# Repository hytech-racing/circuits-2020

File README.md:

# 2020 Circuits

Repository for all of the circuits for the 2019-2020 car.

## Getting Started with this Git Repository
1. Follow HyTech's [Software Guide](https://github.com/hytech-racing/training/tree/master/Resources).
2. Create a GitHub account if you don't already have one.
3. Download and install [GitHub Desktop](https://desktop.github.com/) (basic) or [Git CLI](https://git-scm.com/book/en/v2/Getting-Started-Installing-Git) (advanced).
    * If you are using GitHub Desktop for the first time, be sure to read the [User Guide](https://help.github.com/desktop/guides/).
    * If you are using Git for the first time, you should start off by reading a tutorial. There are many available online:
        * [Pro Git book](https://git-scm.com/book/en/v2)
        * [Atlassian Git Tutorial](https://www.atlassian.com/git/tutorials/)
    * You may want to keep a copy of [GitHub's Git Cheat Sheet](https://services.github.com/kit/downloads/github-git-cheat-sheet.pdf) as a reference.
4. Talk to your subteam lead to be added to the team within the GitHub organization.
5. Clone this repository to your computer using the URLs:
    * SSH: `git@github.com:hytech-racing/circuits-2020.git`
    * HTTPS: `https://github.com/hytech-racing/circuits-2020.git`

## Getting Started with EAGLE
1. Follow HyTech's [Software Guide](https://github.com/hytech-racing/training/tree/master/Resources).
2. Download and install [EAGLE](https://www.autodesk.com/products/eagle/overview)
3. Get the free [Educational License](https://www.autodesk.com/education/free-software/eagle) (a .edu email address is required)

## Circuit Board Versioning Scheme
* New boards must start their numbering at revision 1.
* Revision numbers must be incremented by 1 when a physical board is manufactured, but not at any other time.
* After a board is manufactured, the files corresponding to the manufactured version should not be modified.
* Circuit boards based off of a previous year's design should increment based off of the previous board's revision number.

## More Information
* [Software Guide](https://github.com/hytech-racing/training/tree/master/Resources)
* [Team Site](https://hytechracing.gatech.edu/)
* [Facebook](https://www.facebook.com/HyTechRacing/)
* [Engage](https://gatech.campuslabs.com/engage/organization/hytech-racing)

## License
This project is licensed under the GPL License v3.0. See the [LICENSE](LICENSE) file for more information.

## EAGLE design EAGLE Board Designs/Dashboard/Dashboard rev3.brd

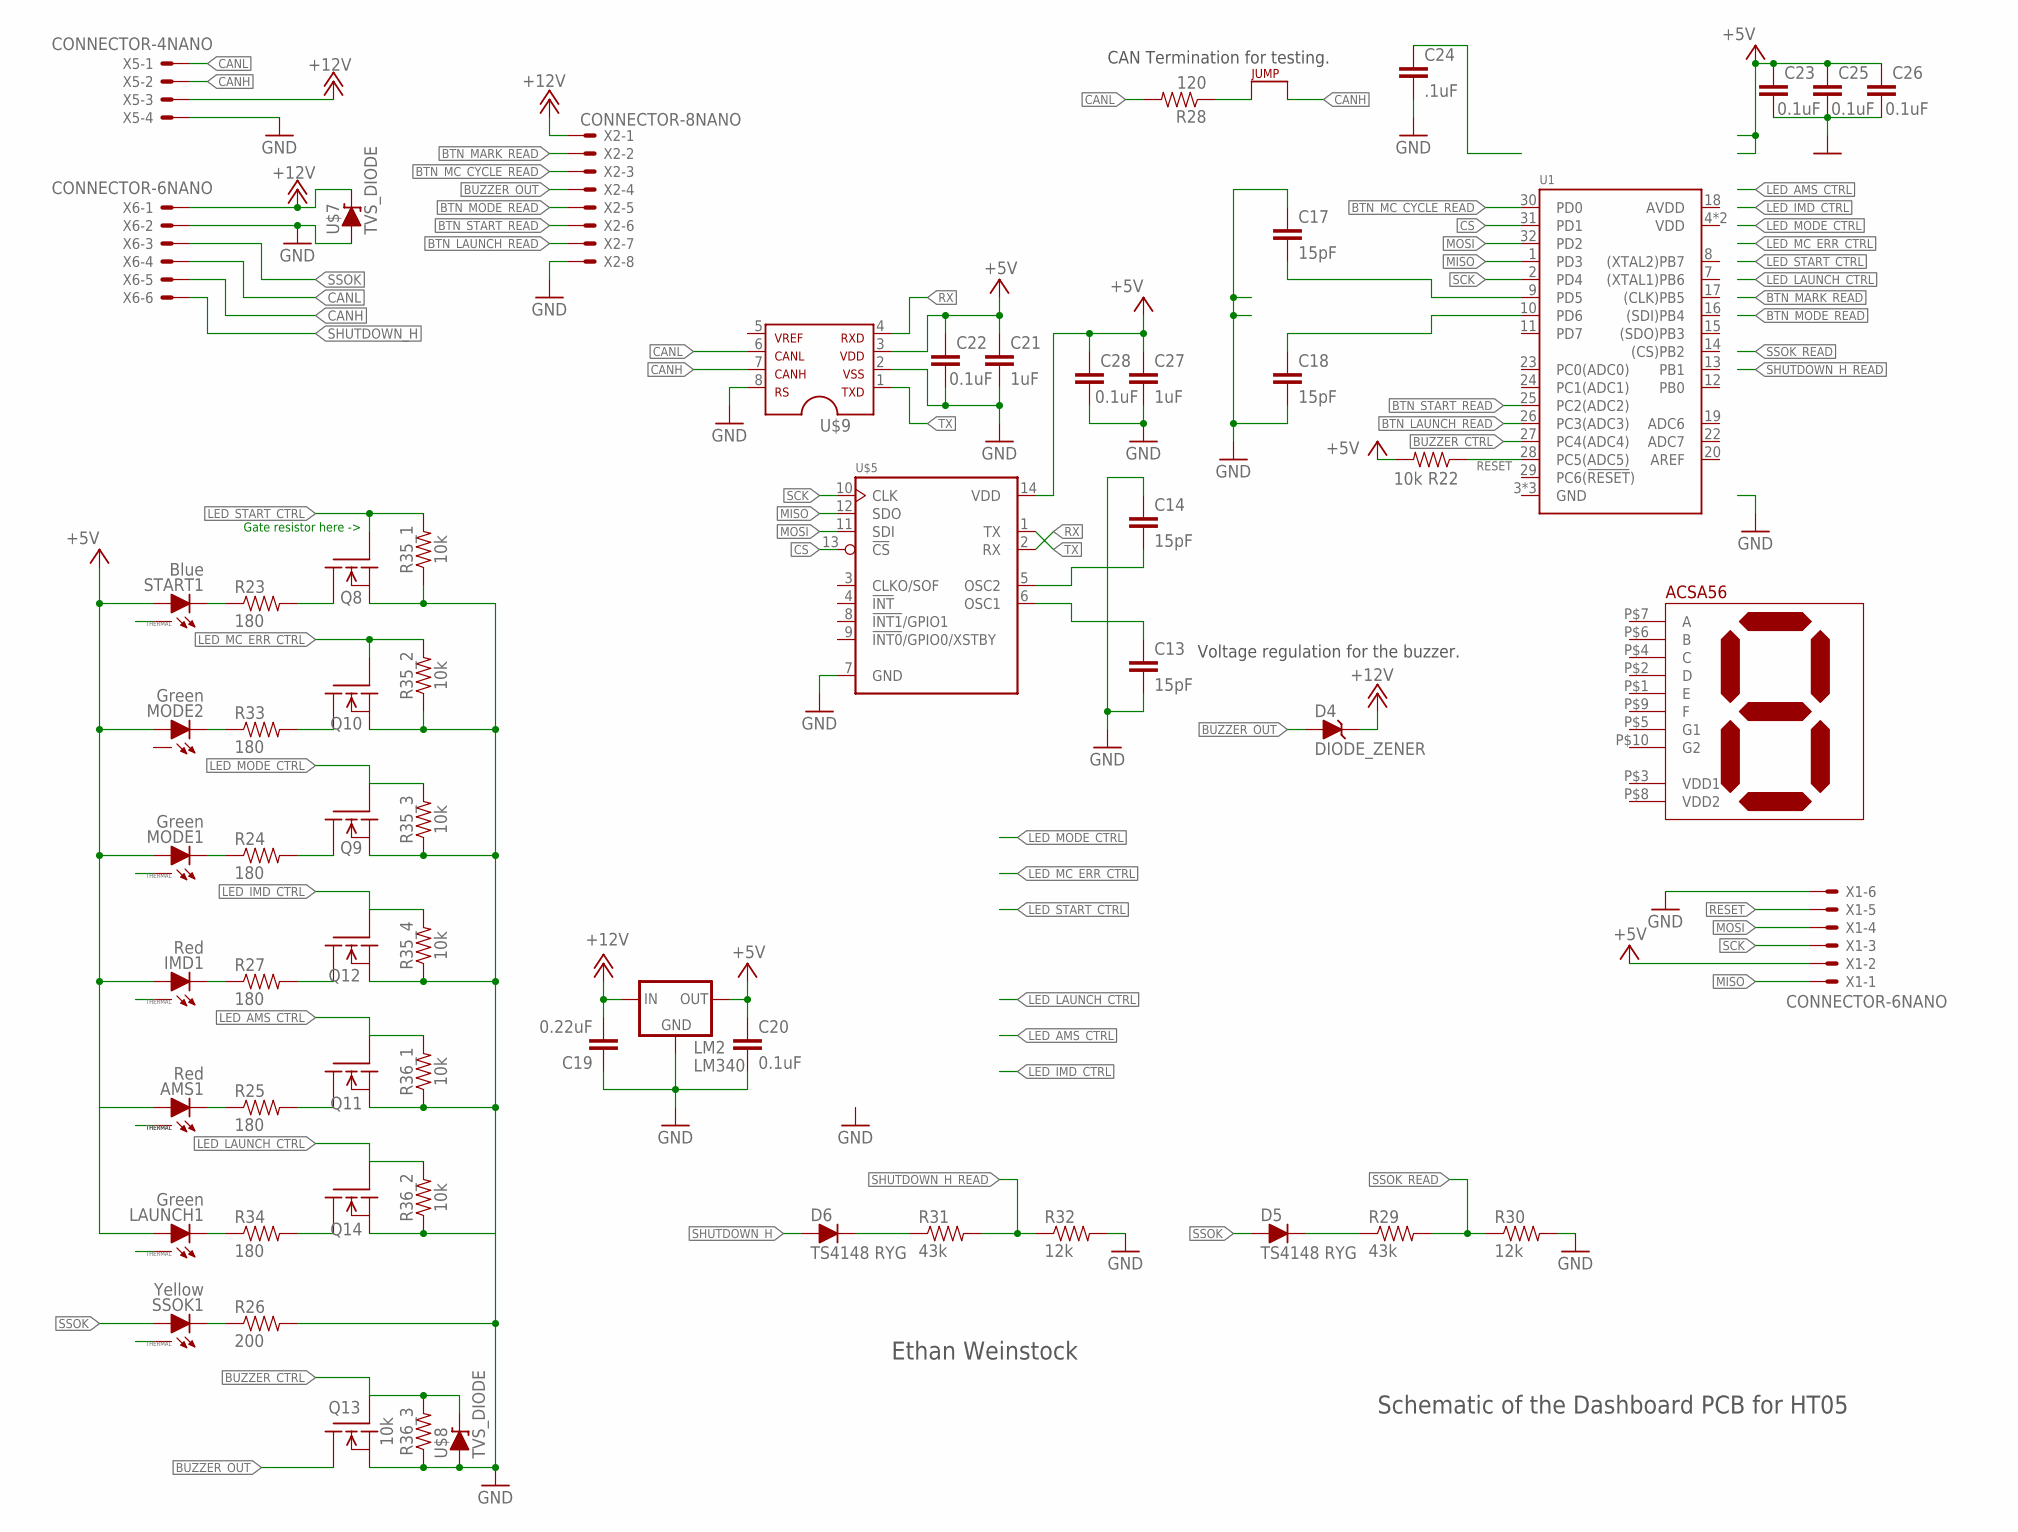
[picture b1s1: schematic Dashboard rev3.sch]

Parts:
AMS1: Red; XP-E2
C13, C14, C17, C18: 15pF; 0603-CAP
C19: 0.22uF; 0603-CAP
C20, C22, C23, C25, C26, C28: 0.1uF; 0603-CAP
C21, C27: 1uF; 0603-CAP
C24: .1uF; 0603-CAP
D4: DIODE_ZENER; SOT23
D5, D6: TS4148 RYG; 0805_D
IMD1: Red; XP-E2
J4: JUMPER0603; 0603-JUMP
LAUNCH1: Green; XP-E2
LM2: LM340; SOT223
MODE1, MODE2: Green; XP-E2
Q8, Q9, Q10, Q11, Q12, Q13, Q14: DMG3406LSOT; SOT23
R22: 10k; 0603-RES
R23, R24, R25, R27, R33, R34: 180; 0603-RES
R26: 200; 0805
R28: 120; 0603-RES
R29, R31: 43k; 0603-RES
R30, R32: 12k; 0603-RES
R35, R36: 10k; CAT16-*4
SSOK1: Yellow; XP-E2
START1: Blue; XP-E2
U1: ATMEGA328P-AU; TQFP-32
U$1: ACSA56-51CGKWA
U$5: MCP2518FD; SOIC-14
U$7, U$8: TVS_DIODE; U-DFN1608-2
U$9: MCP2562FD; SOIC-08
X1, X6: CONNECTOR-6NANO; MOLEX_NANOFIT_SMD_06
X2: CONNECTOR-8NANO; MOLEX_NANOFIT_SMD_08
X5: CONNECTOR-4NANO; MOLEX_NANOFIT_SMD_04

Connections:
+5V: C20.1, C21.1, C22.1, C23.1, C25.1, C26.1, C27.1, C28.1, LM2.3 (OUT), R22.2, U$5.14 (VDD), U$9.3, X1.2
+5V1: AMS1.A, IMD1.A, LAUNCH1.A, MODE1.A, MODE2.A, START1.A
+12V: C19.2, D4.3 (C), LM2.1 (IN), U$7.P$2 (C), X2.1, X5.3, X6.1
AVDD: U1.18 (AVDD)
BTN_LAUNCH_READ: U1.26 (PC3(ADC3)), X2.7
BTN_MARK_READ: X2.2
BTN_MC_CYCLE_READ: U1.30 (PD0), X2.3
BTN_MODE_READ: X2.5
BTN_START_READ: U1.25 (PC2(ADC2)), X2.6
BUZZER_CTRL: Q13.1 (G), R36.P$6 (2), U1.27 (PC4(ADC4)), U$8.P$2 (C)
BUZZER_OUT: D4.1 (A), Q13.3 (D), X2.4
CANH: J4.2, U$9.7, X5.2, X6.5
CANL: R28.2, U$9.6, X5.1, X6.4
CS: U1.31 (PD1), U$5.13 (!CS)
GND: C13.2, C14.1, C17.1, C18.2, C19.1, C20.2, C23.2, C24.2, C25.2, C26.2, C27.2, C28.2, LM2.2 (GND), LM2.4 (GND), Q8.2 (S), Q9.2 (S), Q10.2 (S), Q11.2 (S), Q12.2 (S), Q13.2 (S), R26.2, R30.2, R32.2, R35.P$1 (1), R35.P$2 (1), R35.P$3 (1), R35.P$4 (1), R36.P$1 (1), R36.P$3 (1), U1.3 (GND), U1.5 (GND), U1.21 (GND), U$5.7 (GND), U$7.P$1 (A), U$8.P$1 (A), U$9.8, X1.6, X2.8, X5.4, X6.2
GND2: Q14.2 (S), R36.P$2 (1)
LED_AMS_CTRL: Q11.1 (G), R36.P$8 (2)
LED_IMD_CTRL: Q12.1 (G), R35.P$5 (2)
LED_LAUNCH_CTRL: Q14.1 (G), R36.P$7 (2)
LED_MC_ERR_CTRL: Q10.1 (G), R35.P$7 (2)
LED_MODE_CTRL: Q9.1 (G), R35.P$6 (2)
LED_START_CTRL: Q8.1 (G), R35.P$8 (2)
MISO: U1.1 (PD3), U$5.12 (SDO), X1.1
MOSI: U1.32 (PD2), U$5.11 (SDI), X1.4
unnamed: C13.1, U$5.6 (OSC1)
unnamed: MODE2.C, R33.1
unnamed: C17.2, U1.9 (PD5)
unnamed: C18.1, U1.10 (PD6)
unnamed: MODE1.C, R24.1
unnamed: IMD1.C, R27.1
unnamed: R26.1, SSOK1.C
unnamed: AMS1.C, R25.1
unnamed: R23.1, START1.C
unnamed: D5.C, R29.1
unnamed: D6.C, R31.1
unnamed: Q8.3 (D), R23.2
unnamed: Q10.3 (D), R33.2
unnamed: Q9.3 (D), R24.2
unnamed: Q12.3 (D), R27.2
unnamed: Q11.3 (D), R25.2
unnamed: J4.1, R28.1
unnamed: LAUNCH1.C, R34.1
unnamed: Q14.3 (D), R34.2
unnamed: C14.2, C21.2, C22.2, U$5.5 (OSC2), U$9.2
RESET: R22.1, U1.28 (PC5(ADC5)), X1.5
RX: U$5.2 (RX), U$9.4
SCK: U1.2 (PD4), U$5.10 (CLK), X1.3
SHUTDOWN_H: D6.A, X6.6
SHUTDOWN_H_READ: R31.2, R32.1
SSOK: D5.A, SSOK1.A, X6.3
SSOK_READ: R29.2, R30.1
THERMAL: AMS1.X, IMD1.X, LAUNCH1.X, MODE1.X, SSOK1.X, START1.X
TX: U$5.1 (TX), U$9.1
VDD: U1.4 (VDD), U1.6 (VDD)

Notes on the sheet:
Ethan Weinstock
Schematic of the Dashboard PCB for HT05
Voltage regulation for the buzzer.
CAN Termination for testing.
Gate resistor here ->

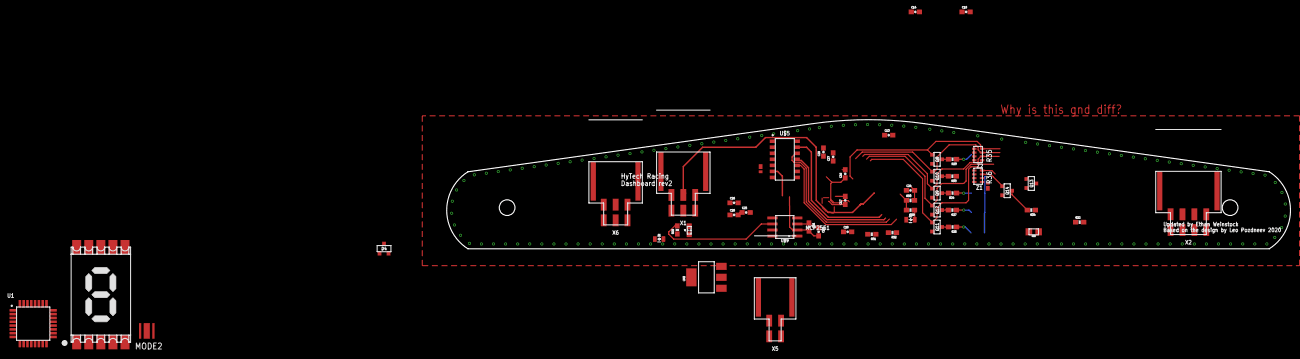
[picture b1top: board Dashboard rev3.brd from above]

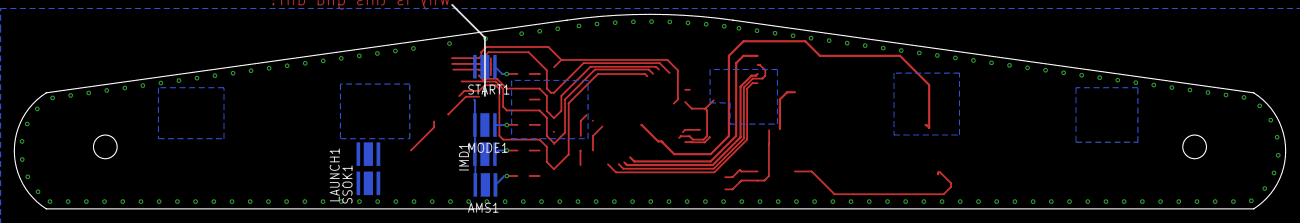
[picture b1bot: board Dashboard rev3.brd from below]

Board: 2 copper layers, 177.4 x 27.1 mm, 58 parts (6 on the bottom side), 51 nets.

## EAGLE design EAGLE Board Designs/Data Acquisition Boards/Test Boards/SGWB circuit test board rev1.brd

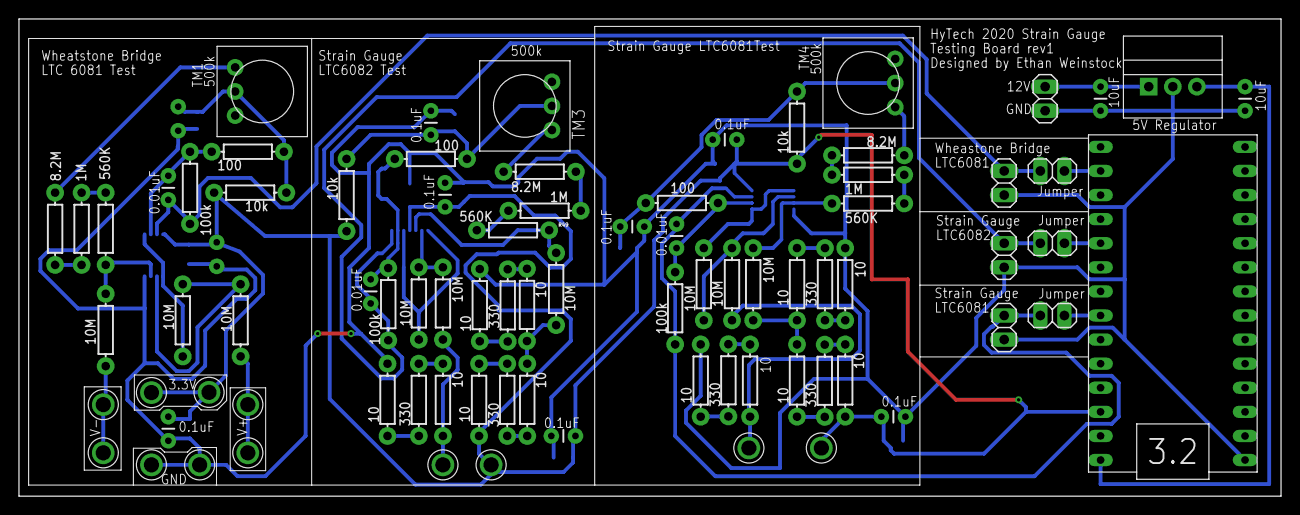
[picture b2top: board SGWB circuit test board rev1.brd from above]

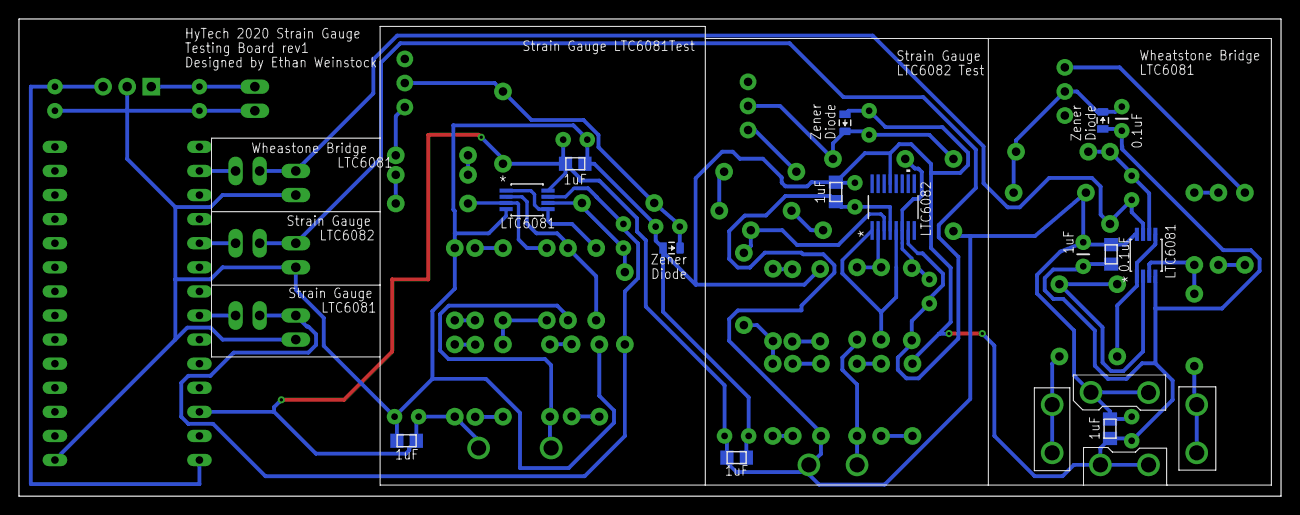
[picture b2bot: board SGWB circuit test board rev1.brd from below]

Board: 2 copper layers, 133.1 x 50.3 mm, 95 parts (14 on the bottom side), 52 nets.

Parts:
C1: 0.1uF; 0805
C2, C14, C29: 0.01uF; CAP-PTH-SMALL
C3, C11, C15, C17, C21, C26, C28, C30: 0.1uF; CAP-PTH-SMALL
C4: 1uF; CAP-PTH-SMALL
C5, C6: 10uF; CAP-PTH-SMALL
C12, C16, C22, C27, C31: 1uF; 0805
J1, J2, J3: JUMPER.1; 1X02
JP1, JP2, JP3, JP4: M02; 1X02
LT1790B, LT1790B2: 1.25V; 0805_D
LT1790B3: DIODE_ZENER0805; 0805_D
R1, R2, R4, R18, R19, R21, R29, R33, R35: 10M; AXIAL-0.3
R3, R20, R34: 8.2M; AXIAL-0.3
R5, R22, R36: 100k; AXIAL-0.3
R6, R23, R37: 100; AXIAL-0.3
R7, R24, R38: 10k; AXIAL-0.3
R8, R15, R16, R17, R25, R28, R31, R32, R40, R42, R43, R45: 10; AXIAL-0.3
R26, R27, R39, R41, R44, R46: 330; AXIAL-0.3
R47, R49, R53: 1M; AXIAL-0.3
R48, R50, R54: 560K; AXIAL-0.3
REG: 5V; OKI-78SR
TM1, TM3, TM4: 500k; TRIM-3386
U1: LTC6082CGNPBF; SSOP-16_GN
U$1, U$9: LTC6081; MSOP-8_MS
U$2: TEENSY_3.2_SIMPLE
U$5, U$6, U$8, U$10, U$11, U$12, U$13, U$14, U$15, U$16, U$17, U$18: TEST_POINT

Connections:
3V3: C1.2, C4.1, C11.1, C12.1, C15.2, C16.1, C21.1, C22.1, C26.1, C27.1, C28.2, C31.1, R7.P$2, R24.P$2, R25.P$1, R28.P$1, R38.P$2, U1.4, U$1.8, U$2.3.3V, U$5.P$1, U$8.P$1, U$9.8, U$11.P$1, U$18.P$1
+5V: C6.2, REG.3, U$2.VIN
+12V: C5.2, JP2.2, REG.1
GND: C1.1, C3.1, C4.2, C5.1, C6.1, C11.2, C12.2, C15.1, C16.2, C17.1, C21.2, C22.2, C26.2, C27.2, C28.1, C30.1, C31.2, JP1.1, JP2.1, JP3.1, JP4.1, LT1790B.A, LT1790B2.A, LT1790B3.A, R40.P$2, R42.P$1, R43.P$2, R45.P$1, REG.2, U1.13, U$1.4, U$2.GND, U$9.4, U$14.P$1, U$15.P$1
INB-: C2.1, R5.P$1, R6.P$2, U$1.6
INB-3: C29.1, R36.P$1, R37.P$2, U$9.6
unnamed: R1.P$2, R4.P$2, U$1.2
unnamed: R2.P$2, R54.P$1, U$1.3
unnamed: C3.2, LT1790B.C, R6.P$1, R7.P$1, TM1.2
unnamed: J1.1, U$2.A0
unnamed: R3.P$2, TM1.1
unnamed: J2.1, U$2.A3
unnamed: J3.1, U$2.A6
unnamed: R16.P$2, R17.P$2, R19.P$1
unnamed: C17.2, LT1790B2.C, R23.P$1, R24.P$1, TM3.2
unnamed: R20.P$2, TM3.1
unnamed: R8.P$2, R26.P$1
unnamed: R27.P$2, R32.P$1
unnamed: R31.P$1, R41.P$2
unnamed: R16.P$1, R44.P$2
unnamed: R31.P$2, R32.P$2, R33.P$1
unnamed: R17.P$1, R39.P$2
unnamed: R25.P$2, R41.P$1
unnamed: R29.P$2, R35.P$2, U$9.2
unnamed: R33.P$2, R48.P$1, U$9.3
unnamed: C30.2, LT1790B3.C, R37.P$1, R38.P$1, TM4.2
unnamed: R34.P$2, TM4.1
unnamed: R26.P$2, R43.P$1
unnamed: R27.P$1, R42.P$2
unnamed: R28.P$2, R44.P$1
unnamed: R39.P$1, R45.P$2
unnamed: R15.P$2, R46.P$1
unnamed: R40.P$1, R46.P$2
unnamed: R34.P$1, R47.P$1
unnamed: R47.P$2, R48.P$2
unnamed: R20.P$1, R49.P$1
unnamed: R49.P$2, R50.P$2
unnamed: R3.P$1, R53.P$1
unnamed: R53.P$2, R54.P$2
OUT1: R4.P$1, U$1.1, U$1.5
OUT3: R35.P$1, U$9.1, U$9.5
OUT4: R21.P$1, U1.1, U1.5
OUT4A+: R19.P$2, R50.P$1, U1.3
OUT4A-: R18.P$2, R21.P$2, U1.2
V+1: R1.P$1, U$12.P$1, U$13.P$1
V-1: R2.P$1, U$16.P$1, U$17.P$1
VOUT1: C2.2, J1.2, JP1.2, R5.P$2, U$1.7
VOUT3: C29.2, J3.2, JP4.2, R36.P$2, U$9.7
VOUT4: C14.2, J2.2, JP3.2, R22.P$2, U1.7
VOUT4-: C14.1, R22.P$1, R23.P$2, U1.6
VR3-2: R8.P$1, R29.P$1, U$6.P$1
VR4-2: R15.P$1, R18.P$1, U$10.P$1

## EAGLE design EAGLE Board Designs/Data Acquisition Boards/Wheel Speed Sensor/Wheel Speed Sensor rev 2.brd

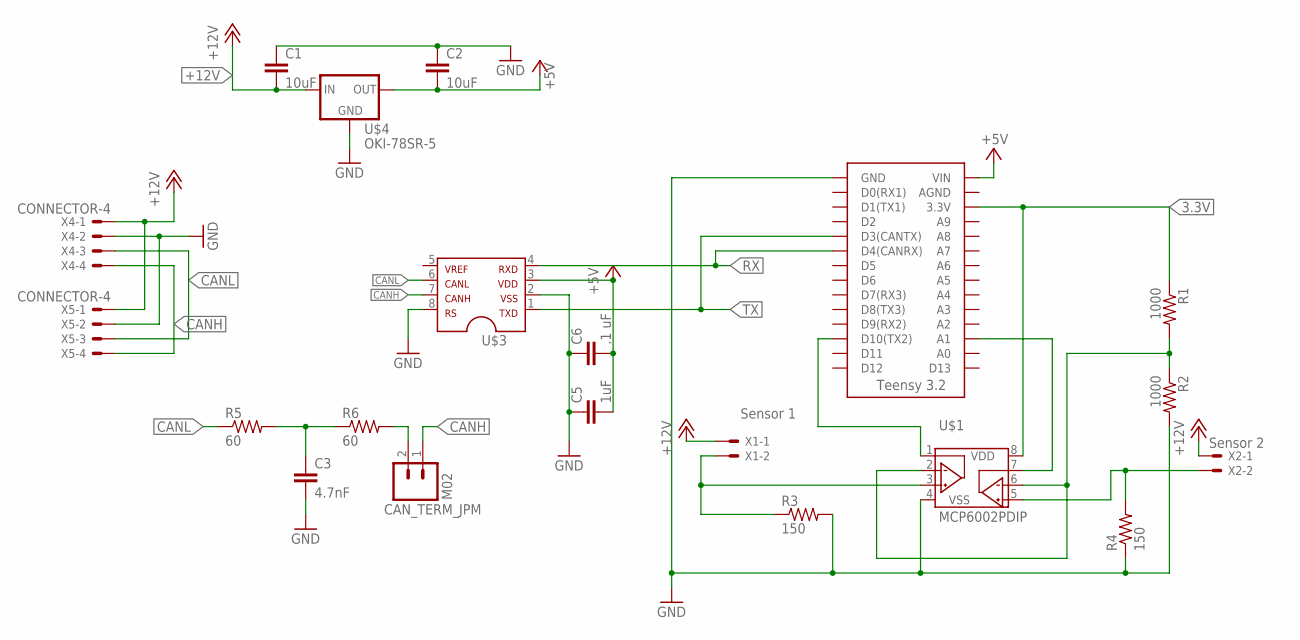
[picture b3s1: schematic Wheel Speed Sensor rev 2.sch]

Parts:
C1, C2: 10uF; CAP-PTH-5MM
C3: 4.7nF; CAP-PTH-5MM
C5: 1uF; CAP-PTH-5MM
C6: .1 uF; CAP-PTH-5MM
CAN_TERM_JPM: M02; 1X02
R1, R2: 1000; AXIAL-0.3
R3, R4: 150; AXIAL-0.3
R5, R6: 60; AXIAL-0.3
U$1: MCP6002PDIP; DIL08
U$2: TEENSY_3.2_SIMPLE
U$3: MCP2551; SOIC-08
U$4: OKI-78SR-5; OKI-78SR
X1: Sensor 1; MINIFIT_5566-2
X2: Sensor 2; MINIFIT_5566-2
X4, X5: CONNECTOR-4; MINIFIT_5566-4

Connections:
3.3V: R1.P$1 (1), U$1.8 (VDD), U$2.3.3V
+5V: C2.2, C5.2, C6.2, U$2.VIN, U$3.3, U$4.3 (OUT)
+12V: C1.2, U$4.1 (IN), X1.1, X2.1, X4.1, X5.1
CANH: CAN_TERM_JPM.1, U$3.7, X4.4, X5.4
CANL: R5.P$1 (1), U$3.6, X4.3, X5.3
GND: C1.1, C2.1, C3.2, C5.1, C6.1, R2.P$2 (2), R3.P$2 (2), R4.P$1 (1), U$1.4 (VSS), U$2.GND, U$3.2, U$3.8, U$4.2 (GND), X4.2, X5.2
unnamed: R1.P$2 (2), R2.P$1 (1), U$1.2 (VINA-), U$1.6 (VINB-)
unnamed: C3.1, R5.P$2 (2), R6.P$1 (1)
unnamed: R3.P$1 (1), U$1.3 (VINA+), X1.2
unnamed: U$1.7 (VOUTB), U$2.A1
unnamed: U$1.1 (VOUTA), U$2.D10(TX2)
unnamed: R4.P$2 (2), U$1.5 (VINB+), X2.2
unnamed: CAN_TERM_JPM.2, R6.P$2 (2)
RX: U$2.D4(CANRX), U$3.4
TX: U$2.D3(CANTX), U$3.1

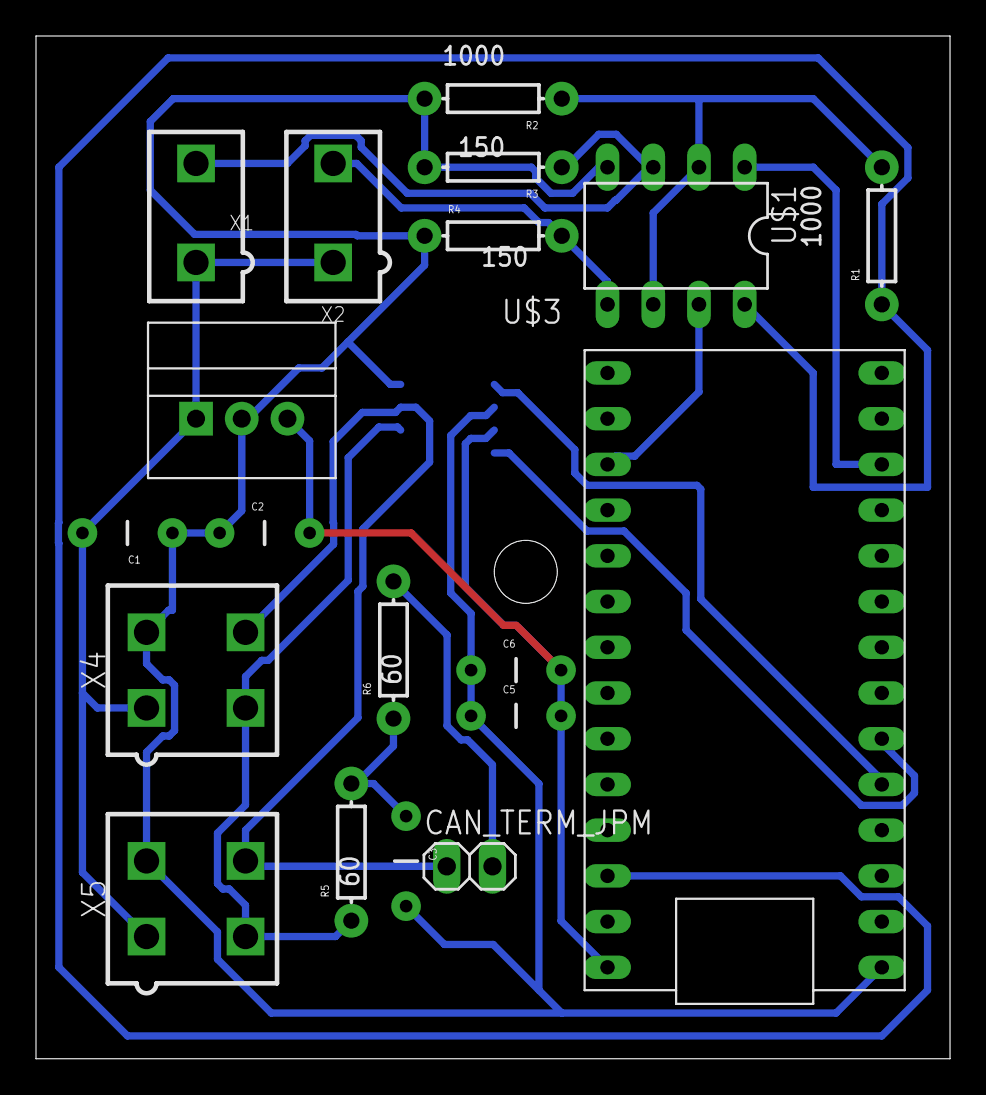
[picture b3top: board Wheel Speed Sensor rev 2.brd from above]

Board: 2 copper layers, 50.8 x 56.8 mm, 20 parts (1 on the bottom side), 15 nets.

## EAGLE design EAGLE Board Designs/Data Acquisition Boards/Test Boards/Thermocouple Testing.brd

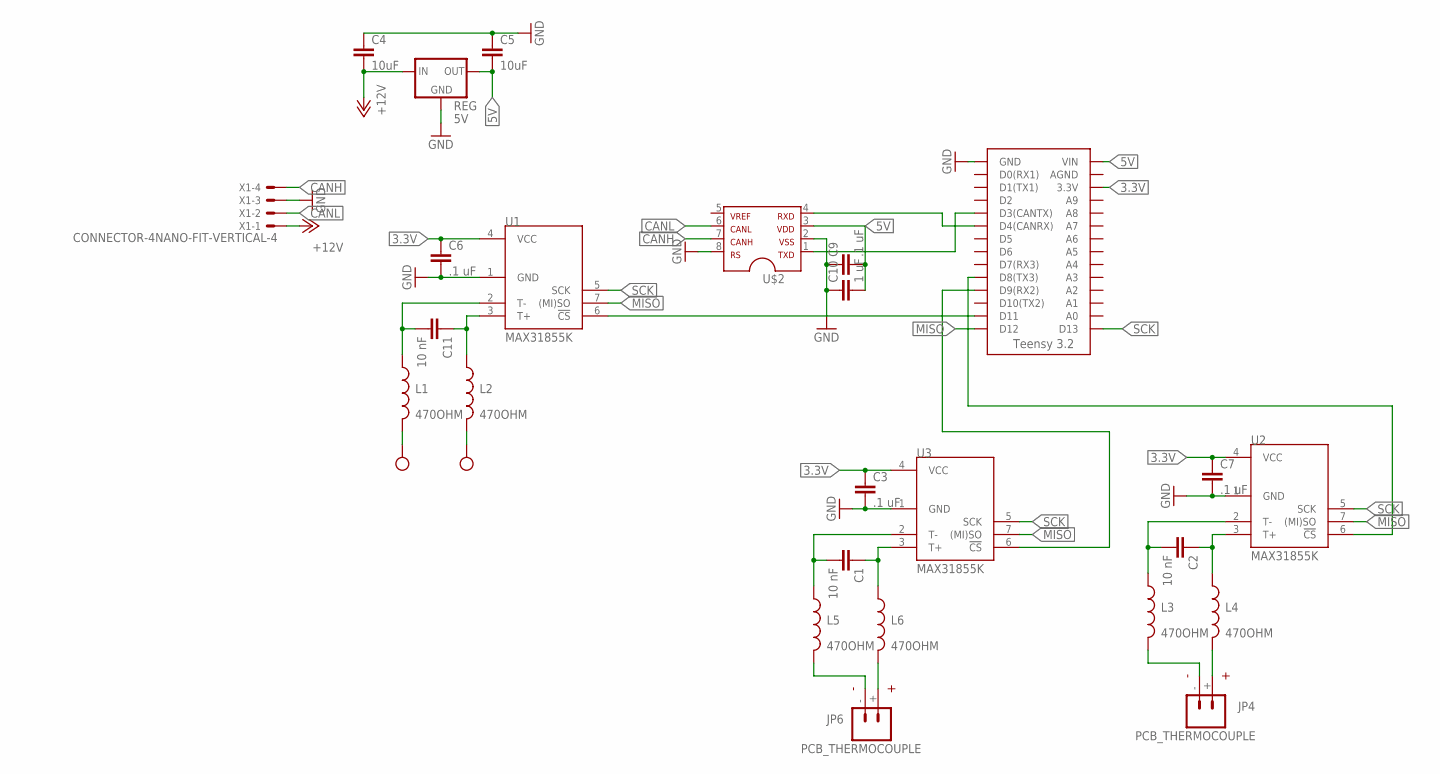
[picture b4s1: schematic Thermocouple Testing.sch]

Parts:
C1, C2, C11: 10 nF; AXIAL-5MM
C3, C6, C7, C9: .1 uF; AXIAL-5MM
C4, C5: 10uF; AXIAL-5MM
C10: 1 uF; AXIAL-5MM
JP4, JP6: PCB_THERMOCOUPLE; PCC-SMP
L1, L2, L3, L4, L5, L6: 470OHM; 0805
REG: 5V; OKI-78SR
U1, U2, U3: MAX31855K; SOIC8
U$1: TEENSY_3.2_SIMPLE
U$2: MCP2551DIL; DIL08
U$3, U$4: TEST_POINT
X1: CONNECTOR-4NANO-FIT-VERTICAL-4; NANO-FIT_VERTICAL-4

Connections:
3.3V: C3.P$1 (1), C6.P$1 (1), C7.P$1 (1), U1.4 (VCC), U2.4 (VCC), U3.4 (VCC), U$1.3.3V
5V: C5.P$2 (2), C9.P$2 (2), C10.P$2 (2), REG.3 (OUT), U$1.VIN, U$2.3
+12V: C4.P$2 (2), REG.1 (IN), X1.P$1
CANH: U$2.7, X1.P$4
CANL: U$2.6, X1.P$2
GND: C3.P$2 (2), C4.P$1 (1), C5.P$1 (1), C6.P$2 (2), C7.P$2 (2), C9.P$1 (1), C10.P$1 (1), REG.2 (GND), U1.1 (GND), U2.1 (GND), U3.1 (GND), U$1.GND, U$2.2, U$2.8, X1.P$3
MISO: U1.7 ((MI)SO), U2.7 ((MI)SO), U3.7 ((MI)SO), U$1.D12
unnamed: L1.2, U$3.P$1
unnamed: L2.2, U$4.P$1
unnamed: C11.P$2 (2), L1.1, U1.2 (T-)
unnamed: C2.P$1 (1), L4.1, U2.3 (T+)
unnamed: C11.P$1 (1), L2.1, U1.3 (T+)
unnamed: U1.6 (!CS), U$1.D11
unnamed: U3.6 (!CS), U$1.D9(RX2)
unnamed: U2.6 (!CS), U$1.D8(TX3)
unnamed: C2.P$2 (2), L3.1, U2.2 (T-)
unnamed: JP4.-, L3.2
unnamed: JP4.+, L4.2
unnamed: C1.P$1 (1), L6.1, U3.3 (T+)
unnamed: U$1.D3(CANTX), U$2.1
unnamed: U$1.D4(CANRX), U$2.4
unnamed: C1.P$2 (2), L5.1, U3.2 (T-)
unnamed: JP6.-, L5.2
unnamed: JP6.+, L6.2
SCK: U1.5 (SCK), U2.5 (SCK), U3.5 (SCK), U$1.D13

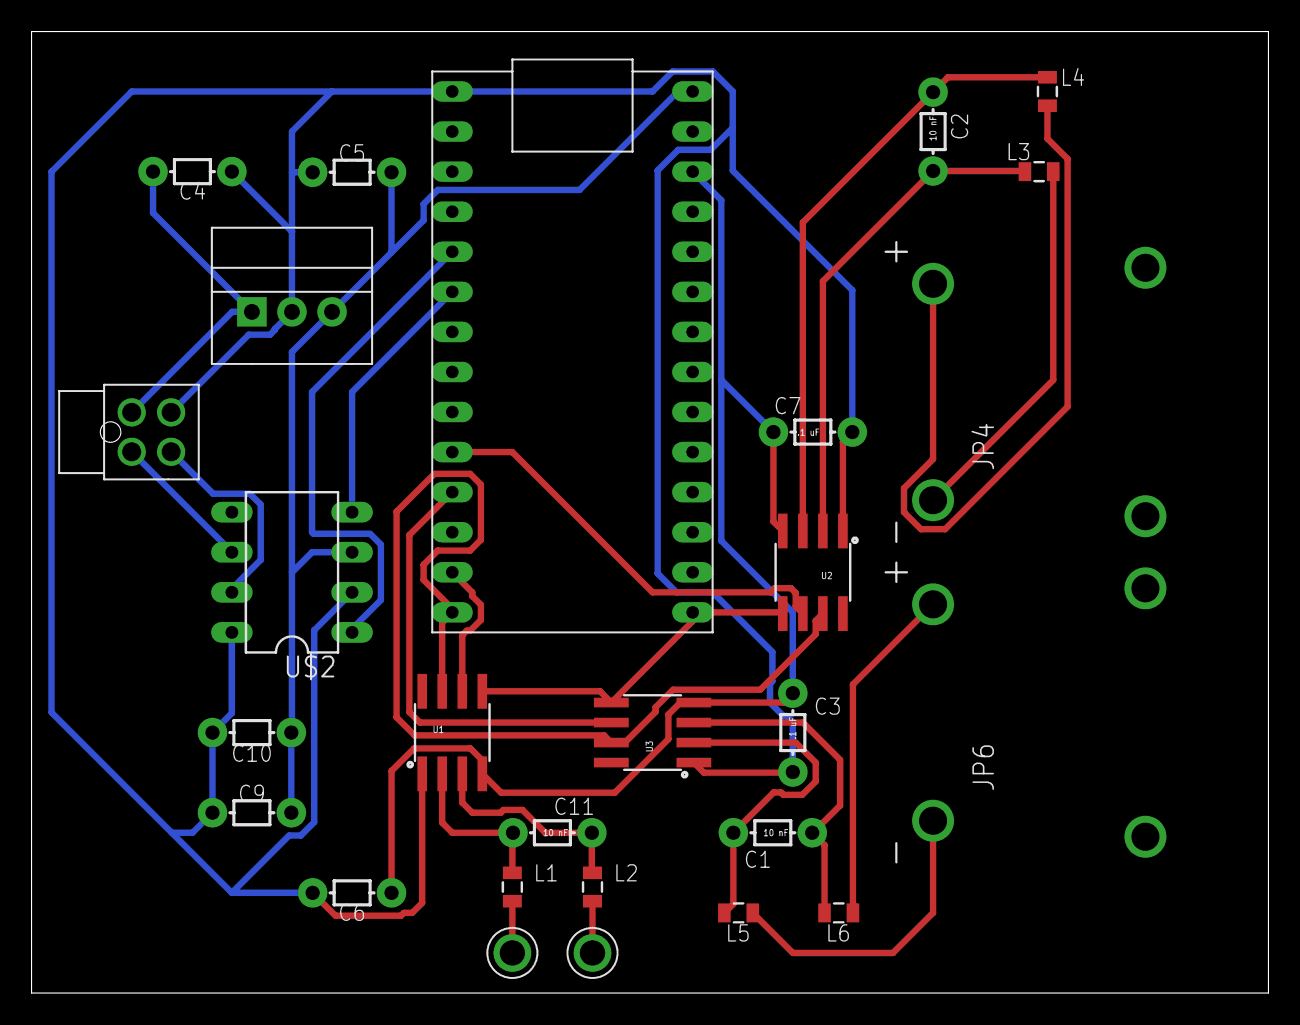
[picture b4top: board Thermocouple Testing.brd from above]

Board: 2 copper layers, 78.4 x 61.0 mm, 27 parts (0 on the bottom side), 25 nets.

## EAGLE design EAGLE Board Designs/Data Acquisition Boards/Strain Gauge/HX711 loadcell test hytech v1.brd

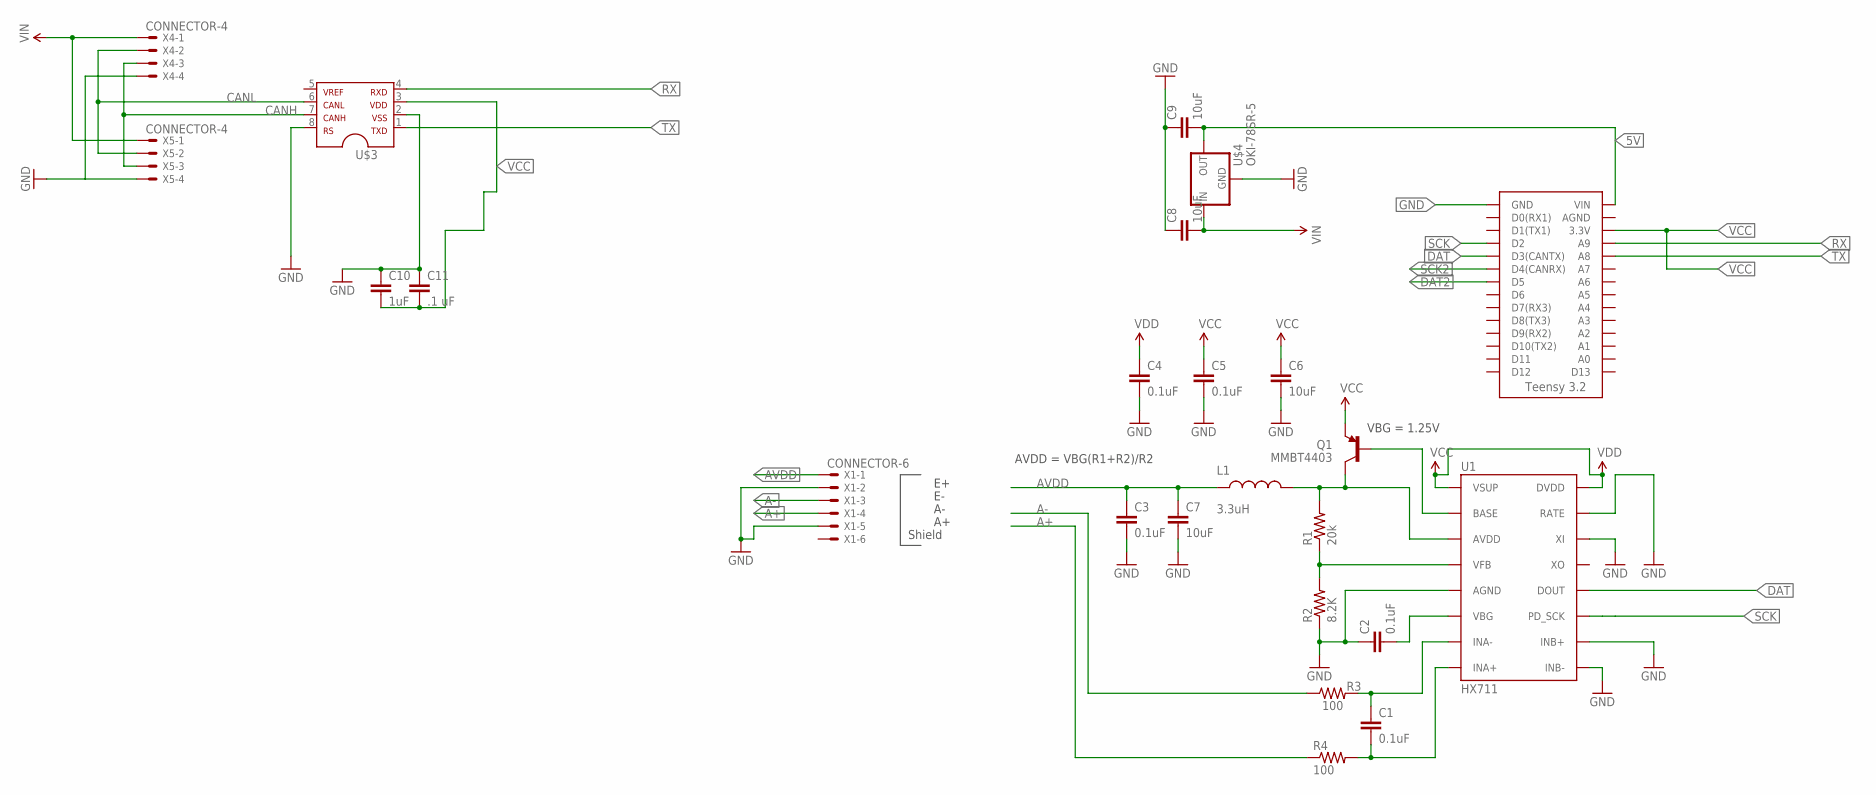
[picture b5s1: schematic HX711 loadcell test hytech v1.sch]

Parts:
C1, C2, C3, C4, C5: 0.1uF; 0603-CAP
C6, C7: 10uF; 1210
C8, C9: 10uF; 0805
C10: 1uF; 0805
C11: .1 uF; 0805
L1: 3.3uH; 0805
Q1: MMBT4403; SOT23-3
R1: 20k; 0603-RES
R2: 8.2K; 0603-RES
R3, R4: 100; 0603-RES
U1: HX711; SO16
U$1: TEENSY_3.2_SIMPLE
U$3: MCP2551; SOIC-08
U$4: OKI-78SR-5; OKI-78SR
X1: CONNECTOR-6; MINIFIT_5566-6
X4, X5: CONNECTOR-4; MINIFIT_5566-4

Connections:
5V: C9.2, U$1.VIN, U$4.3 (OUT)
A+: R4.1, X1.4
A-: R3.1, X1.3
AVDD: C3.1, C7.1, L1.1, X1.1
CANH: U$3.7, X4.3, X5.3
CANL: U$3.6, X4.2, X5.2
DAT: U1.12 (DOUT), U$1.D3(CANTX)
DAT2: U$1.D5
GND: C2.1, C3.2, C4.2, C5.2, C6.2, C7.2, C8.1, C9.1, C10.1, C11.1, R2.1, U1.5 (AGND), U1.9 (INB-), U1.10 (INB+), U1.14 (XI), U1.15 (RATE), U$1.GND, U$3.2, U$3.8, U$4.2 (GND), X1.2, X1.5, X4.4, X5.4
unnamed: C1.1, R3.2, U1.7 (INA-)
unnamed: C1.2, R4.2, U1.8 (INA+)
unnamed: Q1.1 (B), U1.2 (BASE)
unnamed: L1.2, Q1.3 (C), R1.2, U1.3 (AVDD)
unnamed: R1.1, R2.2, U1.4 (VFB)
unnamed: C2.2, U1.6 (VBG)
RX: U$1.A9, U$3.4
SCK: U1.11 (PD_SCK), U$1.D2
SCK2: U$1.D4(CANRX)
TX: U$1.A8, U$3.1
VCC: C5.1, C6.1, C10.2, C11.2, Q1.2 (E), U1.1 (VSUP), U1.16 (DVDD), U$1.3.3V, U$3.3
VDD: C4.1
VIN: C8.2, U$4.1 (IN), X4.1, X5.1

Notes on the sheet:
VBG = 1.25V
AVDD = VBG(R1+R2)/R2
Shield

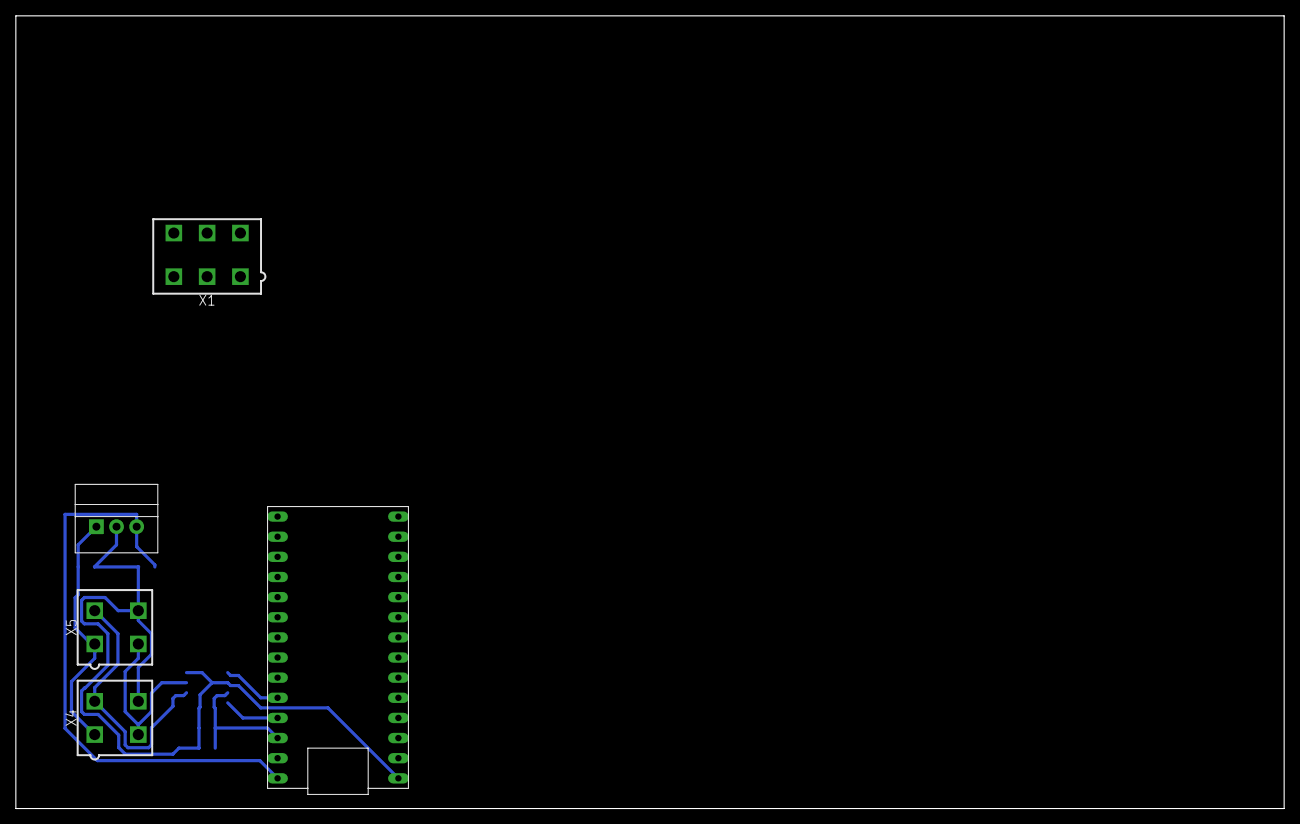
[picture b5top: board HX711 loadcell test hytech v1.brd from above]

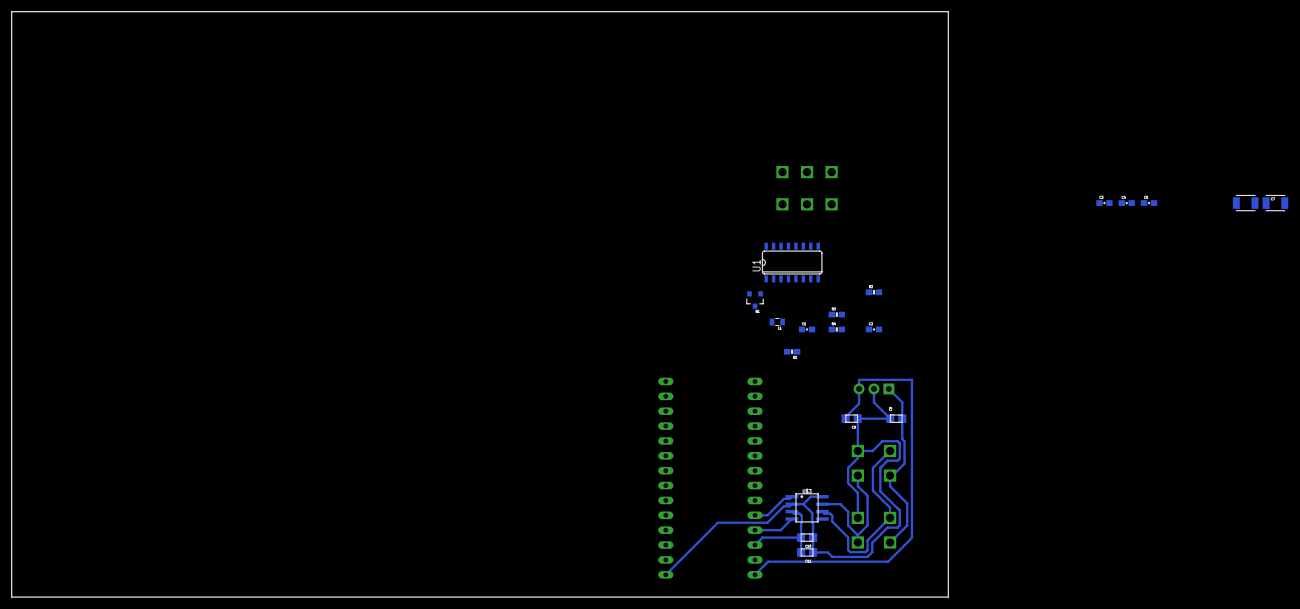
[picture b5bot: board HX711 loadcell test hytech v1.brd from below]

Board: 2 copper layers, 160.0 x 100.0 mm, 24 parts (19 on the bottom side), 19 nets.

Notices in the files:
parts and their libraries:
SparkFun-Capacitors: Licensing: Creative Commons ShareAlike 4.0 International - https://creativecommons.org/licenses/by-sa/4.0
SparkFun-Aesthetics: Licensing: CC v3.0 Share-Alike You are welcome to use this library for commercial purposes.
